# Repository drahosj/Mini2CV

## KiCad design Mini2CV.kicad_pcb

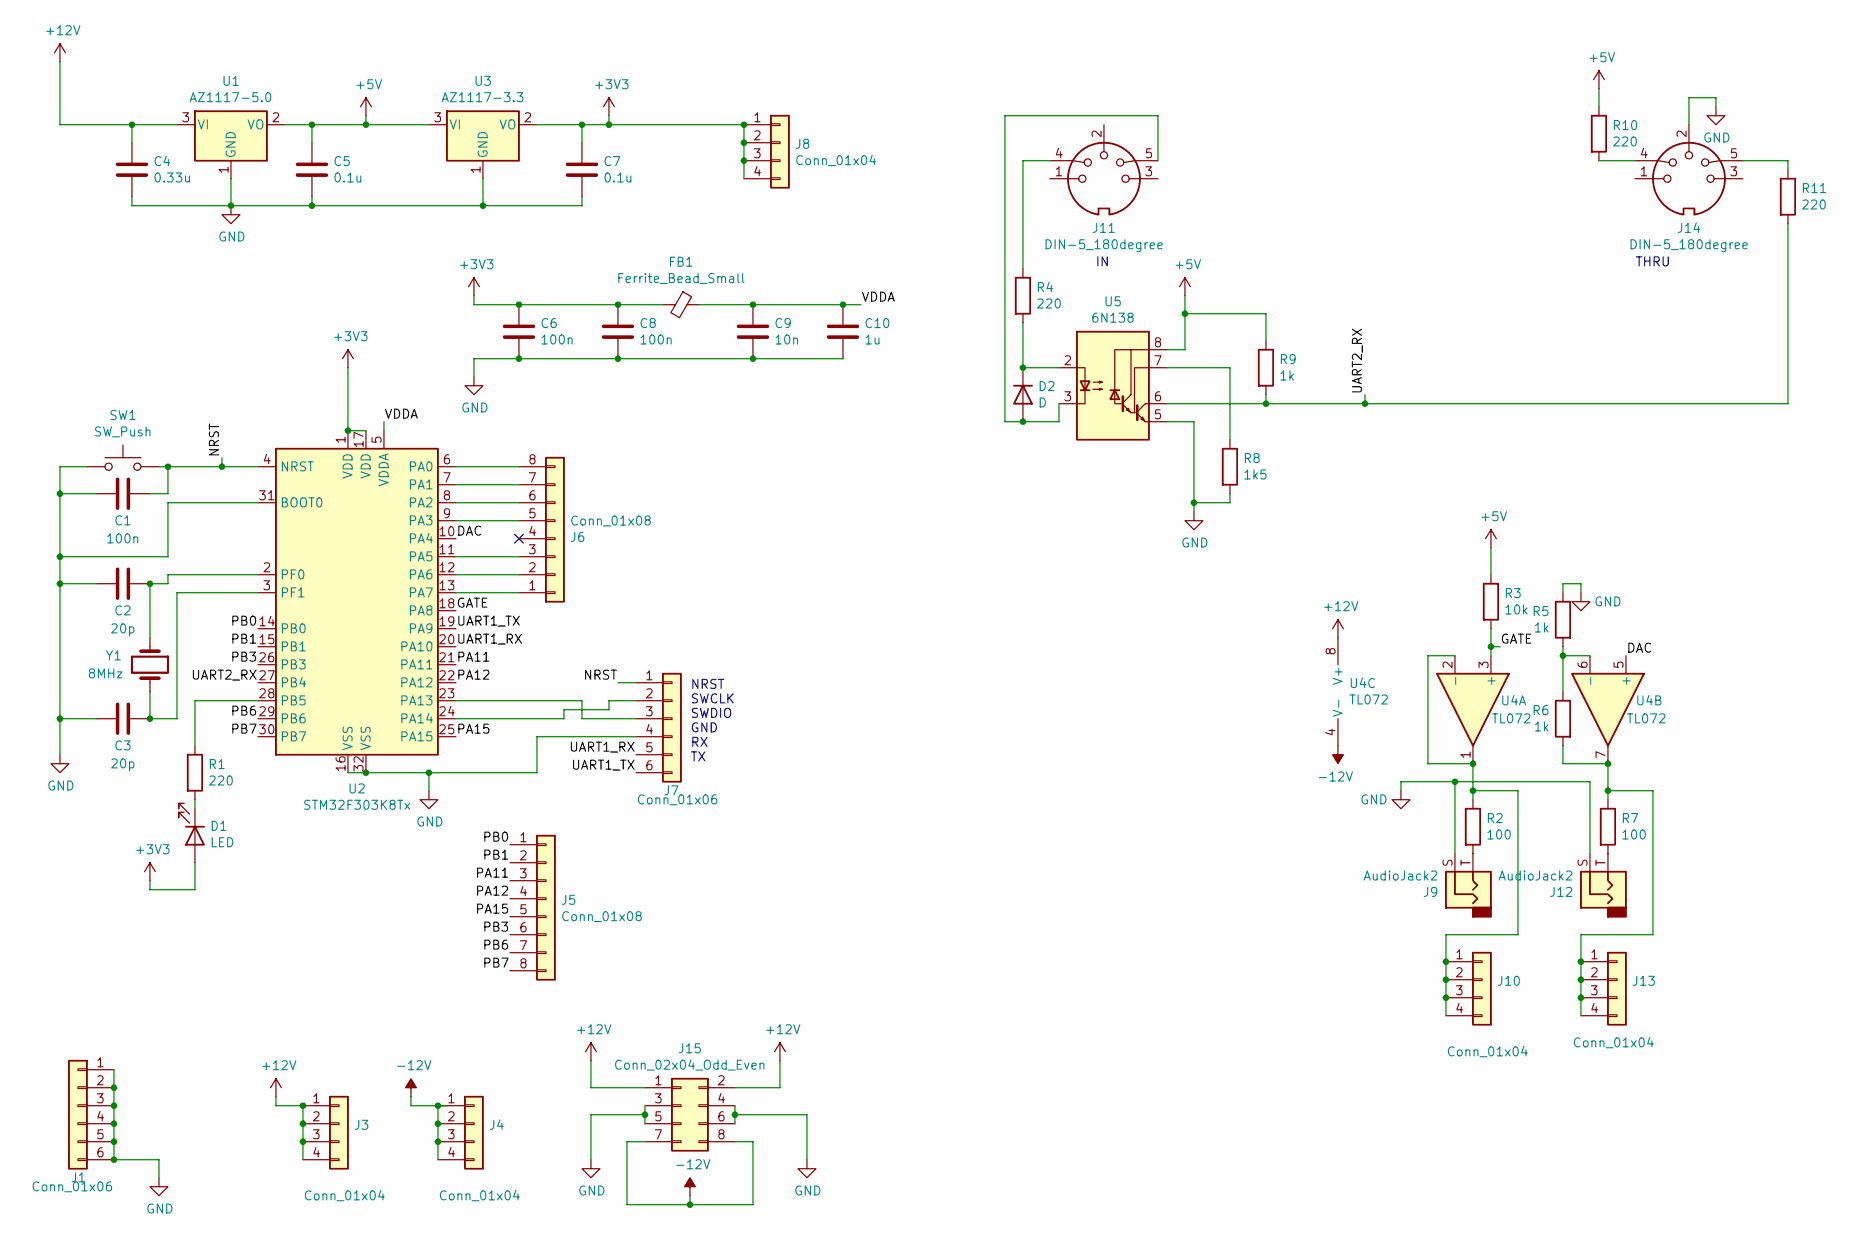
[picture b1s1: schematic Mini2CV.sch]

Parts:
C1, C6, C8: 100n; C_0805_2012Metric_Pad1.18x1.45mm_HandSolder
C2, C3: 20p; C_0805_2012Metric_Pad1.18x1.45mm_HandSolder
C4: 0.33u; C_0805_2012Metric_Pad1.18x1.45mm_HandSolder
C5, C7: 0.1u; C_0805_2012Metric_Pad1.18x1.45mm_HandSolder
C9: 10n; C_0805_2012Metric_Pad1.18x1.45mm_HandSolder
C10: 1u; C_0805_2012Metric_Pad1.18x1.45mm_HandSolder
D1: LED; LED_D5.0mm
D2: D; D_DO-15_P10.16mm_Horizontal
FB1: Ferrite_Bead_Small; L_0805_2012Metric_Pad1.15x1.40mm_HandSolder
J1, J7: Conn_01x06; PinHeader_1x06_P2.54mm_Vertical
J3, J4, J8, J10, J13: Conn_01x04; PinHeader_1x04_P2.54mm_Vertical
J5, J6: Conn_01x08; PinHeader_1x08_P2.54mm_Vertical
J9, J12: AudioJack2; Jack_3.5mm_QingPu_WQP-PJ398SM_Vertical_CircularHoles
J11, J14: DIN-5_180degree; MIDI_DIN5
J15: Conn_02x04_Odd_Even; PinSocket_2x04_P2.54mm_Vertical
R1, R4, R10, R11: 220; R_Axial_DIN0207_L6.3mm_D2.5mm_P10.16mm_Horizontal
R2, R7: 100; R_Axial_DIN0207_L6.3mm_D2.5mm_P10.16mm_Horizontal
R3: 10k; R_0805_2012Metric_Pad1.20x1.40mm_HandSolder
R5, R6, R9: 1k; R_0805_2012Metric_Pad1.20x1.40mm_HandSolder
R8: 1k5; R_Axial_DIN0207_L6.3mm_D2.5mm_P10.16mm_Horizontal
SW1: SW_Push; SW_PUSH_6mm
U1: AZ1117-5.0; SOT-223-3_TabPin2
U2: STM32F303K8Tx; LQFP-32_7x7mm_P0.8mm
U3: AZ1117-3.3; SOT-223-3_TabPin2
U4: TL072; DIP-8_W7.62mm
U5: 6N138; DIP-8_W7.62mm
Y1: 8MHz; Crystal_SMD_HC49-SD_HandSoldering

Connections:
+3V3: C6.1, C7.1, C8.1, D1.2 (A), FB1.2, J8.1, J8.2, J8.3, J8.4, U2.1 (VDD), U2.17 (VDD), U3.2 (VO)
+5V: C5.1, R3.1, R9.1, R10.1, U1.2 (VO), U3.3 (VI), U5.8 (VCC)
+12V: C4.1, J3.1, J3.2, J3.3, J3.4, J15.1, J15.2, U1.3 (VI), U4.8 (V+)
-12V: J4.1, J4.2, J4.3, J4.4, J15.7, J15.8, U4.4 (V-)
/DAC: U2.10 (PA4), U4.5 (+)
/GATE: R3.2, U2.18 (PA8), U4.3 (+)
/NRST: C1.1, J7.1, SW1.2, U2.4 (NRST)
/PA11: J5.3, U2.21 (PA11)
/PA12: J5.4, U2.22 (PA12)
/PA15: J5.5, U2.25 (PA15)
/PB0: J5.1, U2.14 (PB0)
/PB1: J5.2, U2.15 (PB1)
/PB3: J5.6, U2.26 (PB3)
/PB6: J5.7, U2.29 (PB6)
/PB7: J5.8, U2.30 (PB7)
/UART1_RX: J7.5, U2.20 (PA10)
/UART1_TX: J7.6, U2.19 (PA9)
/UART2_RX: R9.2, R11.2, U2.27 (PB4), U5.6 (VO2)
/VDDA: C9.1, C10.1, FB1.1, U2.5 (VDDA)
GND: C1.2, C2.2, C3.2, C4.2, C5.2, C6.2, C7.2, C8.2, C9.2, C10.2, J1.1, J1.2, J1.3, J1.4, J1.5, J1.6, J7.4, J9.S, J12.S, J14.2, J15.3, J15.4, J15.5, J15.6, R5.1, R8.2, SW1.1, U1.1 (GND), U2.16 (VSS), U2.31 (BOOT0), U2.32 (VSS), U3.1 (GND), U5.5 (GND)
unnamed: C2.1, U2.2 (PF0), Y1.1
unnamed: C3.1, U2.3 (PF1), Y1.2
unnamed: D1.1 (K), R1.2
unnamed: D2.1 (K), R4.2, U5.2 (C1)
unnamed: D2.2 (A), J11.5, U5.3 (C2)
unnamed: J6.1, U2.13 (PA7)
unnamed: J6.2, U2.12 (PA6)
unnamed: J6.3, U2.11 (PA5)
unnamed: J6.5, U2.9 (PA3)
unnamed: J6.6, U2.8 (PA2)
unnamed: J6.7, U2.7 (PA1)
unnamed: J6.8, U2.6 (PA0)
unnamed: J7.2, U2.24 (PA14)
unnamed: J7.3, U2.23 (PA13)
unnamed: J9.T, R2.2
unnamed: J10.1, J10.2, J10.3, J10.4, R2.1, U4.1, U4.2 (-)
unnamed: J11.4, R4.1
unnamed: J12.T, R7.2
unnamed: J13.1, J13.2, J13.3, J13.4, R6.2, R7.1, U4.7
unnamed: J14.4, R10.2
unnamed: J14.5, R11.1
unnamed: R1.1, U2.28 (PB5)
unnamed: R5.2, R6.1, U4.6 (-)
unnamed: R8.1, U5.7 (VO1)

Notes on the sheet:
NRST SWCLK SWDIO GND RX TX
THRU

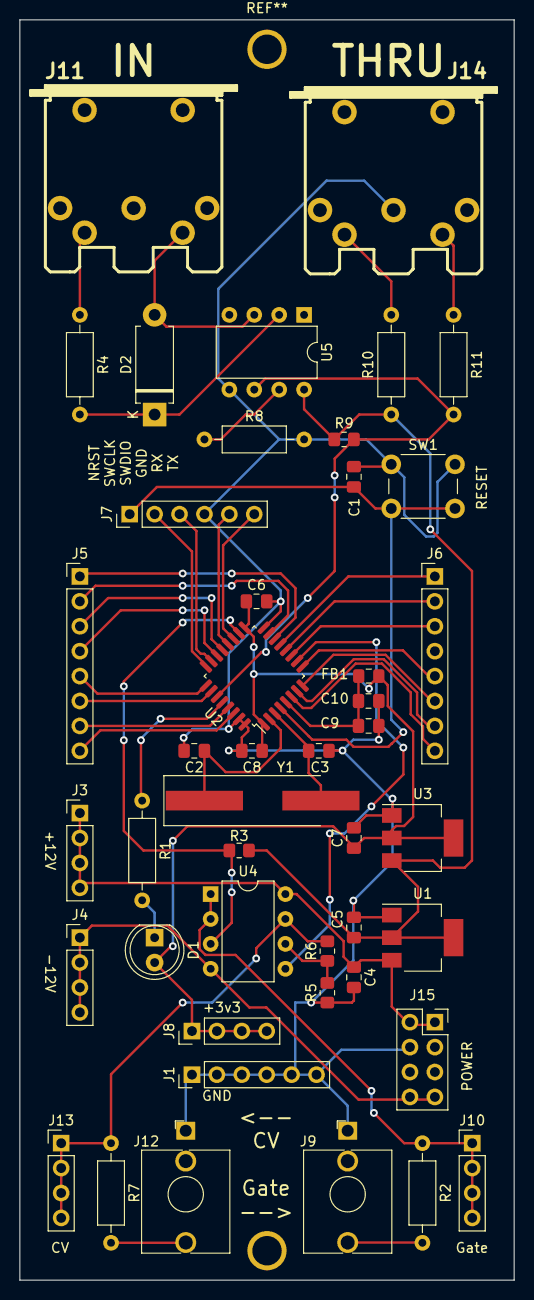
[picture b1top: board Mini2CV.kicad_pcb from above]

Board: 2 copper layers, 50.4 x 128.5 mm, 45 parts (0 on the bottom side), 44 nets.

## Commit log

2020-12-15 Done.
2020-12-30 Commit for upload
